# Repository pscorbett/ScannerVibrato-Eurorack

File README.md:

# ScannerVibrato-Eurorack
Scanner vibrato eurorack module that uses digital logic chips (no MCU) to perform the scanning across the LC ladder.

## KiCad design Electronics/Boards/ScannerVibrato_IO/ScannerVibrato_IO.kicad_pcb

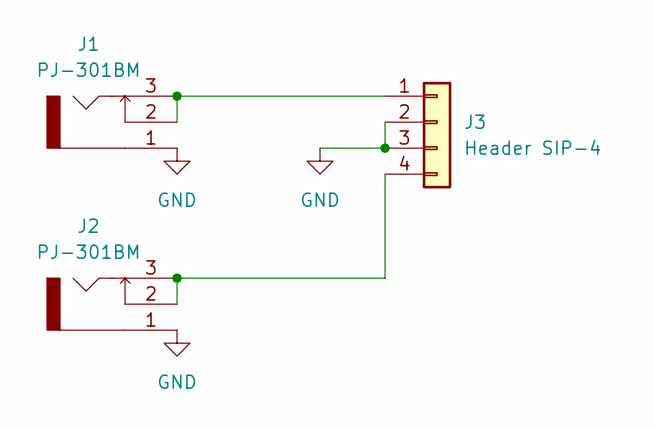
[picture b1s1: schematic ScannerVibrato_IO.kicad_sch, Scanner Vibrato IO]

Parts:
J1, J2: PJ-301BM; Part Number PJ-301BM
J3: Header SIP-4; PinHeader_1x04_P2.54mm_Vertical; Part Number PH1-04-UA

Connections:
GND: J1.1 (S), J2.1 (S), J3.2, J3.3
unnamed: J1.2 (SW), J1.3 (T), J3.1
unnamed: J2.2 (SW), J2.3 (T), J3.4

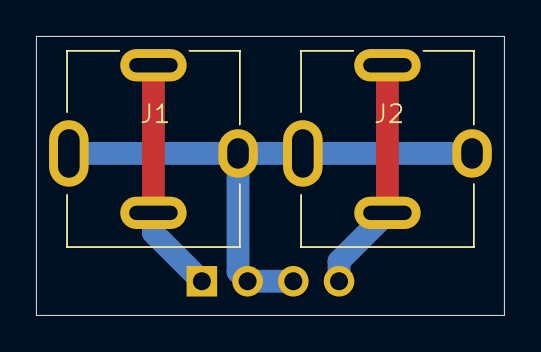
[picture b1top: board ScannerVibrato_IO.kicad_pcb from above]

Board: 2 copper layers, 26.0 x 15.5 mm, 3 parts (1 on the bottom side), 3 nets.

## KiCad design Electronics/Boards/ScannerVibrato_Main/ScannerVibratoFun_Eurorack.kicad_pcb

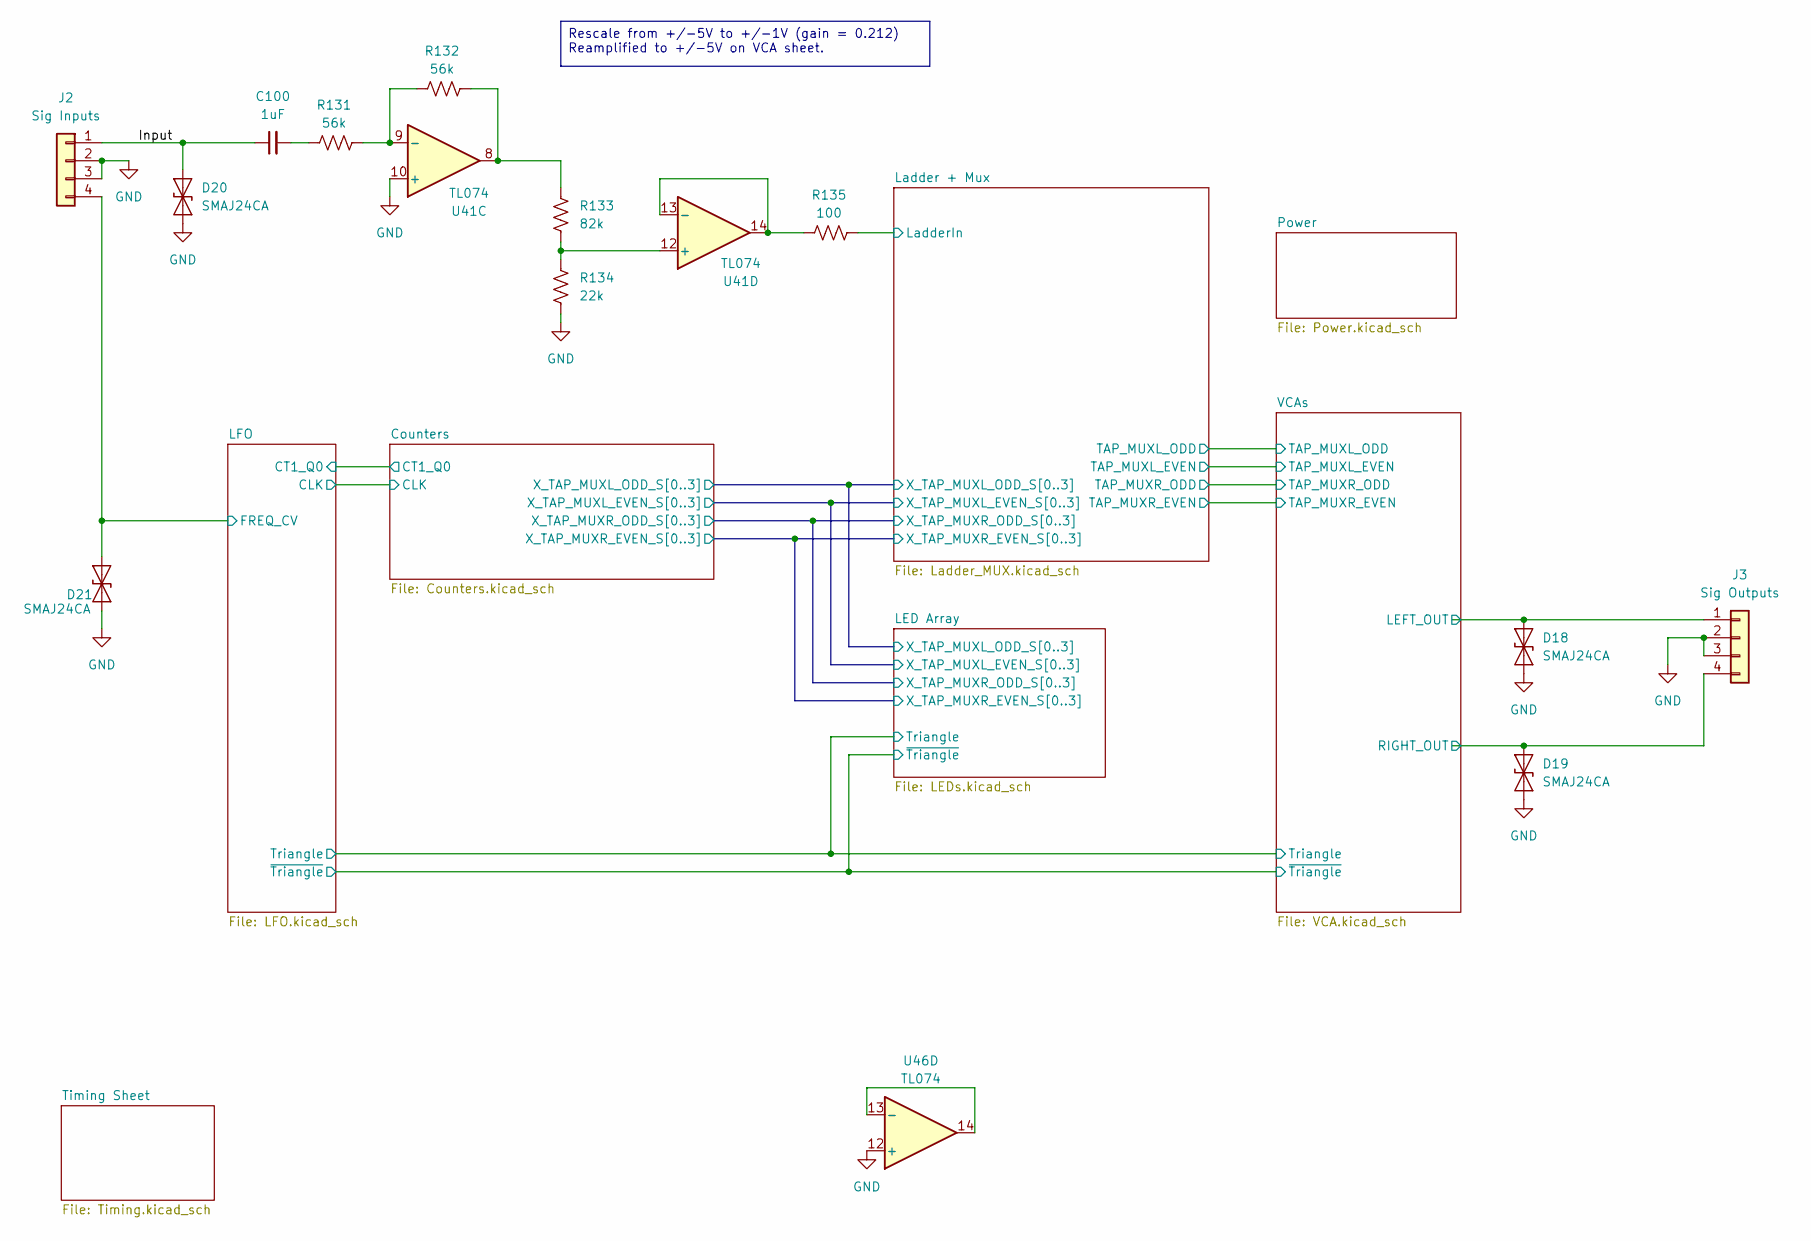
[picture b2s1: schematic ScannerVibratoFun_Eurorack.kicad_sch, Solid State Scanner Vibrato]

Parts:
C100: 1uF; C_0805_2012Metric
D18, D19, D20, D21: SMAJ24CA; D_SMA
J2: Sig Inputs; IO_Jack_Header
J3: Sig Outputs; IO_Jack_Header
R131, R132: 56k; R_0603_1608Metric
R133: 82k; R_0603_1608Metric
R134: 22k; R_0603_1608Metric
R135: 100; R_0603_1608Metric
U41, U46: TL074; TSSOP-14_4.4x5mm_P0.65mm; Part Number TL074HIPWR

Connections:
/Input: C100.1, D20.2 (A2), J2.1
/LFO/FREQ_CV: D21.2 (A2), J2.4; also elsewhere on the board
/Ladder + Mux/LadderIn: R135.2; also elsewhere on the board
/VCAs/LEFT_OUT: D18.2 (A2), J3.1; also elsewhere on the board
/VCAs/RIGHT_OUT: D19.2 (A2), J3.4; also elsewhere on the board
GND: D18.1 (A1), D19.1 (A1), D20.1 (A1), D21.1 (A1), J2.2, J2.3, J3.2, J3.3, R134.1, U41.10 (+), U46.12 (+); also elsewhere on the board
unnamed: C100.2, R131.1
unnamed: R132.2, R133.2, U41.8
unnamed: R131.2, R132.1, U41.9 (-)
unnamed: R133.1, R134.2, U41.12 (+)
unnamed: R135.1, U41.13 (-), U41.14
unnamed: U46.13 (-), U46.14

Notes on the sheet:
Rescale from +/-5V to +/-1V (gain = 0.212) Reamplified to +/-5V on VCA sheet.

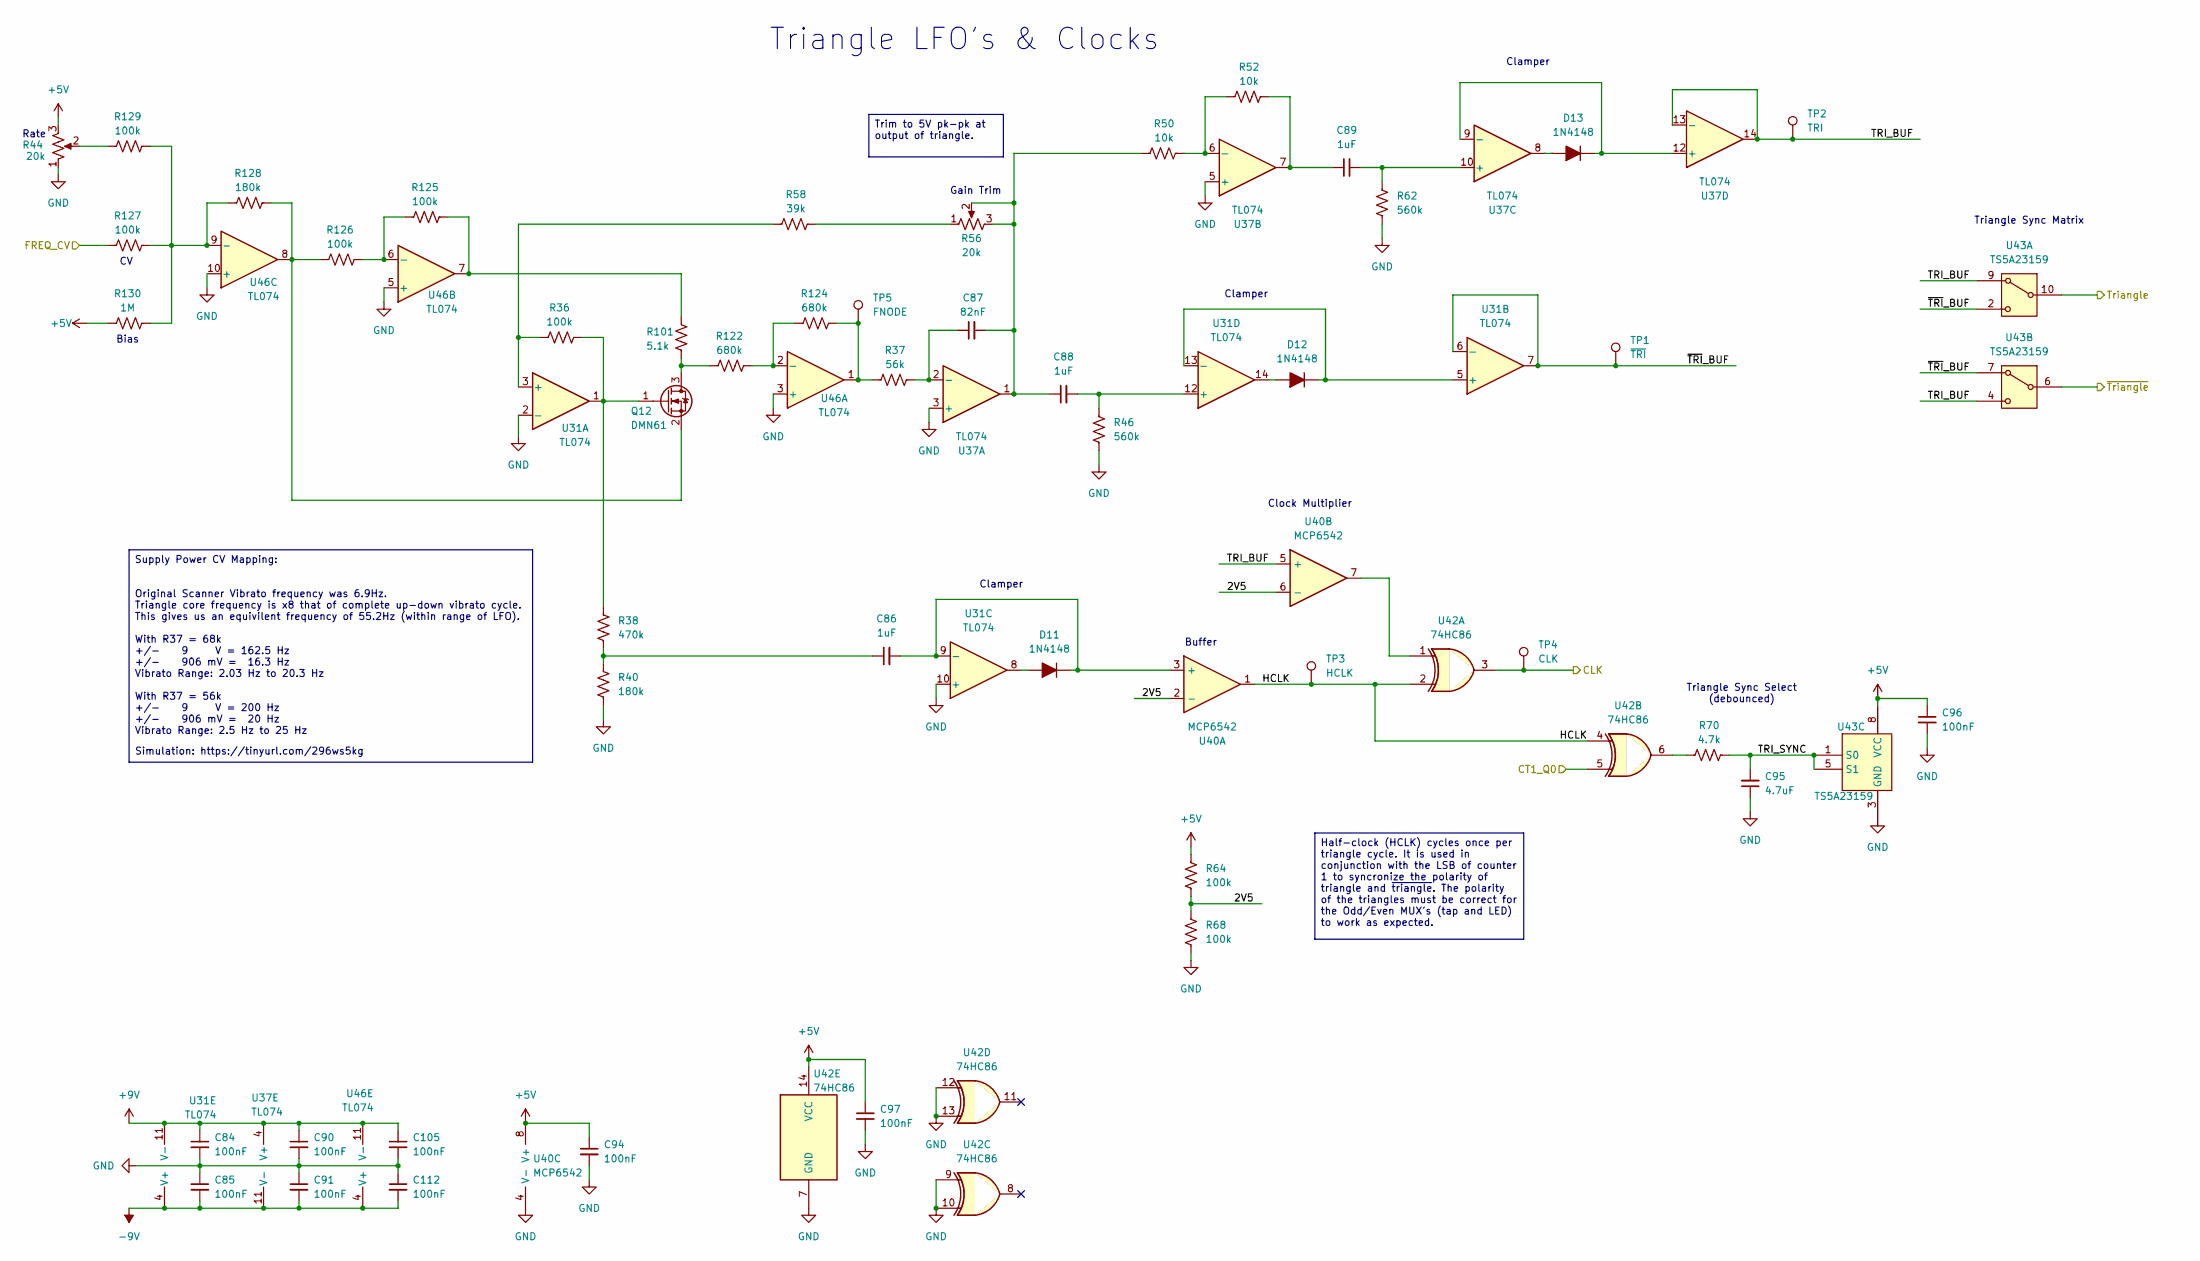
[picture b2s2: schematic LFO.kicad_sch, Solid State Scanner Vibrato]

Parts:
C84, C85, C90, C91, C94, C96, C97, C105, C112: 100nF; C_0603_1608Metric
C86, C88, C89: 1uF; C_0805_2012Metric
C87: 82nF; C_0805_2012Metric
C95: 4.7uF; C_0805_2012Metric
D11, D12, D13: 1N4148; D_SOD-523; Part Number 1N4148WT
Q12: DMN61; SOT-23; Part Number DMN61D9UWQ-13
R36, R64, R68, R125, R126, R127, R129: 100k; R_0603_1608Metric
R37: 56k; R_0603_1608Metric
R38: 470k; R_0603_1608Metric
R40, R128: 180k; R_0603_1608Metric
R44: 20k; 16mm-POT-Right-Angle_LL; Part Number RV16AF-4M-15R1-B20K-EV
R46, R62: 560k; R_0603_1608Metric
R50, R52: 10k; R_0603_1608Metric
R56: 20k; Potentiometer_Bourns_TC33X_Vertical_Fixed3D; Part Number TC33X-2-203E
R58: 39k; R_0603_1608Metric
R70: 4.7k; R_0603_1608Metric
R101: 5.1k; R_0603_1608Metric
R122, R124: 680k; R_0603_1608Metric
R130: 1M; R_0603_1608Metric
TP1: ~{TRI}; 5016; Part Number 5016
TP2: TRI; 5016; Part Number 5016
TP3: HCLK; 5016; Part Number 5016
TP4: CLK; 5016; Part Number 5016
TP5: FNODE; 5016; Part Number 5016
U31, U37, U46: TL074; TSSOP-14_4.4x5mm_P0.65mm; Part Number TL074HIPWR
U40: MCP6542; MSOP-8_3x3mm_P0.65mm; Part Number MCP6542T-I/MS
U42: 74HC86; TSSOP-14_4.4x5mm_P0.65mm; Part Number SN74HC86PWR
U43: TS5A23159; VSSOP-10_3x3mm_P0.5mm; Part Number TS5A23159DGSR

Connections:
+5V: C94.1, C96.1, C97.1, R44.3, R64.2, R130.1, U40.8 (V+), U42.14 (VCC), U43.8 (VCC); also elsewhere on the board
+9V: C84.1, C90.1, C105.1, U31.11 (V-), U37.4 (V+), U46.11 (V-); also elsewhere on the board
-9V: C85.2, C91.2, C112.2, U31.4 (V+), U37.11 (V-), U46.4 (V+); also elsewhere on the board
/Counters/CLK: TP4.1, U42.3; also elsewhere on the board
/Counters/CT1_Q0: U42.5; also elsewhere on the board
/LED Array/Triangle: U43.10 (COM0); also elsewhere on the board
/LED Array/~Triangle: U43.6 (COM1); also elsewhere on the board
/LFO/2V5: R64.1, R68.2, U40.2 (-), U40.6 (-)
/LFO/FREQ_CV: R127.1; also elsewhere on the board
/LFO/HCLK: TP3.1, U40.1, U42.2, U42.4
/LFO/TRI_BUF: TP2.1, U37.13 (-), U37.14, U40.5 (+), U43.4 (NO0), U43.9 (NC0)
/LFO/TRI_SYNC: C95.2, R70.2, U43.1 (S0), U43.5 (S1)
/LFO/~TRI_BUF: TP1.1, U31.6 (-), U31.7, U43.2 (NO0), U43.7 (NC1)
GND: C84.2, C85.1, C90.2, C91.1, C94.2, C95.1, C96.2, C97.2, C105.2, C112.1, R40.1, R44.1, R46.1, R62.1, R68.1, U31.2 (-), U31.10 (+), U37.3 (+), U37.5 (+), U40.4 (V-), U42.7 (GND), U42.9, U42.10, U42.12, U42.13, U43.3 (GND), U46.3 (+), U46.5 (+), U46.10 (+); also elsewhere on the board
unnamed: C86.1, R38.1, R40.2
unnamed: C87.2, C88.1, R50.1, R56.2, R56.3, U37.1
unnamed: C89.1, R52.2, U37.7
unnamed: D11.2 (A), U31.8
unnamed: C86.2, D11.1 (K), U31.9 (-), U40.3 (+)
unnamed: D12.2 (A), U31.14
unnamed: D12.1 (K), U31.5 (+), U31.13 (-)
unnamed: D13.2 (A), U37.8
unnamed: D13.1 (K), U37.9 (-), U37.12 (+)
unnamed: Q12.3 (D), R101.1, R122.1
unnamed: Q12.1 (G), R36.2, R38.2, U31.1
unnamed: Q12.2 (S), R126.1, R128.2, U46.8
unnamed: R56.1, R58.2
unnamed: R70.1, U42.6
unnamed: R101.2, R125.2, U46.7
unnamed: R37.1, R124.2, TP5.1, U46.1
unnamed: R44.2, R129.1
unnamed: R36.1, R58.1, U31.3 (+)
unnamed: C88.2, R46.2, U31.12 (+)
unnamed: C87.1, R37.2, U37.2 (-)
unnamed: R50.2, R52.1, U37.6 (-)
unnamed: C89.2, R62.2, U37.10 (+)
unnamed: U40.7, U42.1
unnamed: R122.2, R124.1, U46.2 (-)
unnamed: R125.1, R126.2, U46.6 (-)
unnamed: R127.2, R128.1, R129.2, R130.2, U46.9 (-)

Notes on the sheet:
Triangle LFO's & Clocks
Clamper
Triangle Sync Select (debounced)
Triangle Sync Matrix
Buffer
Bias
Gain Trim
Clock Multiplier
Simulation: https://tinyurl.com/296ws5kg
Rate
Half-clock (HCLK) cycles once per triangle cycle. It is used in conjunction with the LSB of counter 1 to syncronize the polarity of triangle and ~{triangle}. The polarity of the triangles must be correct for the Odd/Even MUX's (tap and LED) to work as expected.
Trim to 5V pk-pk at output of triangle.
Supply Power CV Mapping: Original Scanner Vibrato frequency was 6.9Hz. Triangle core frequency is x8 that of complete up-down vibrato cycle. This gives us an equivilent frequency of 55.2Hz (within range of LFO). With R37 = 68k +/- 9 V = 162.5 Hz +/- 906 mV = 16.3 Hz Vibrato Range: 2.03 Hz to 20.3 H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

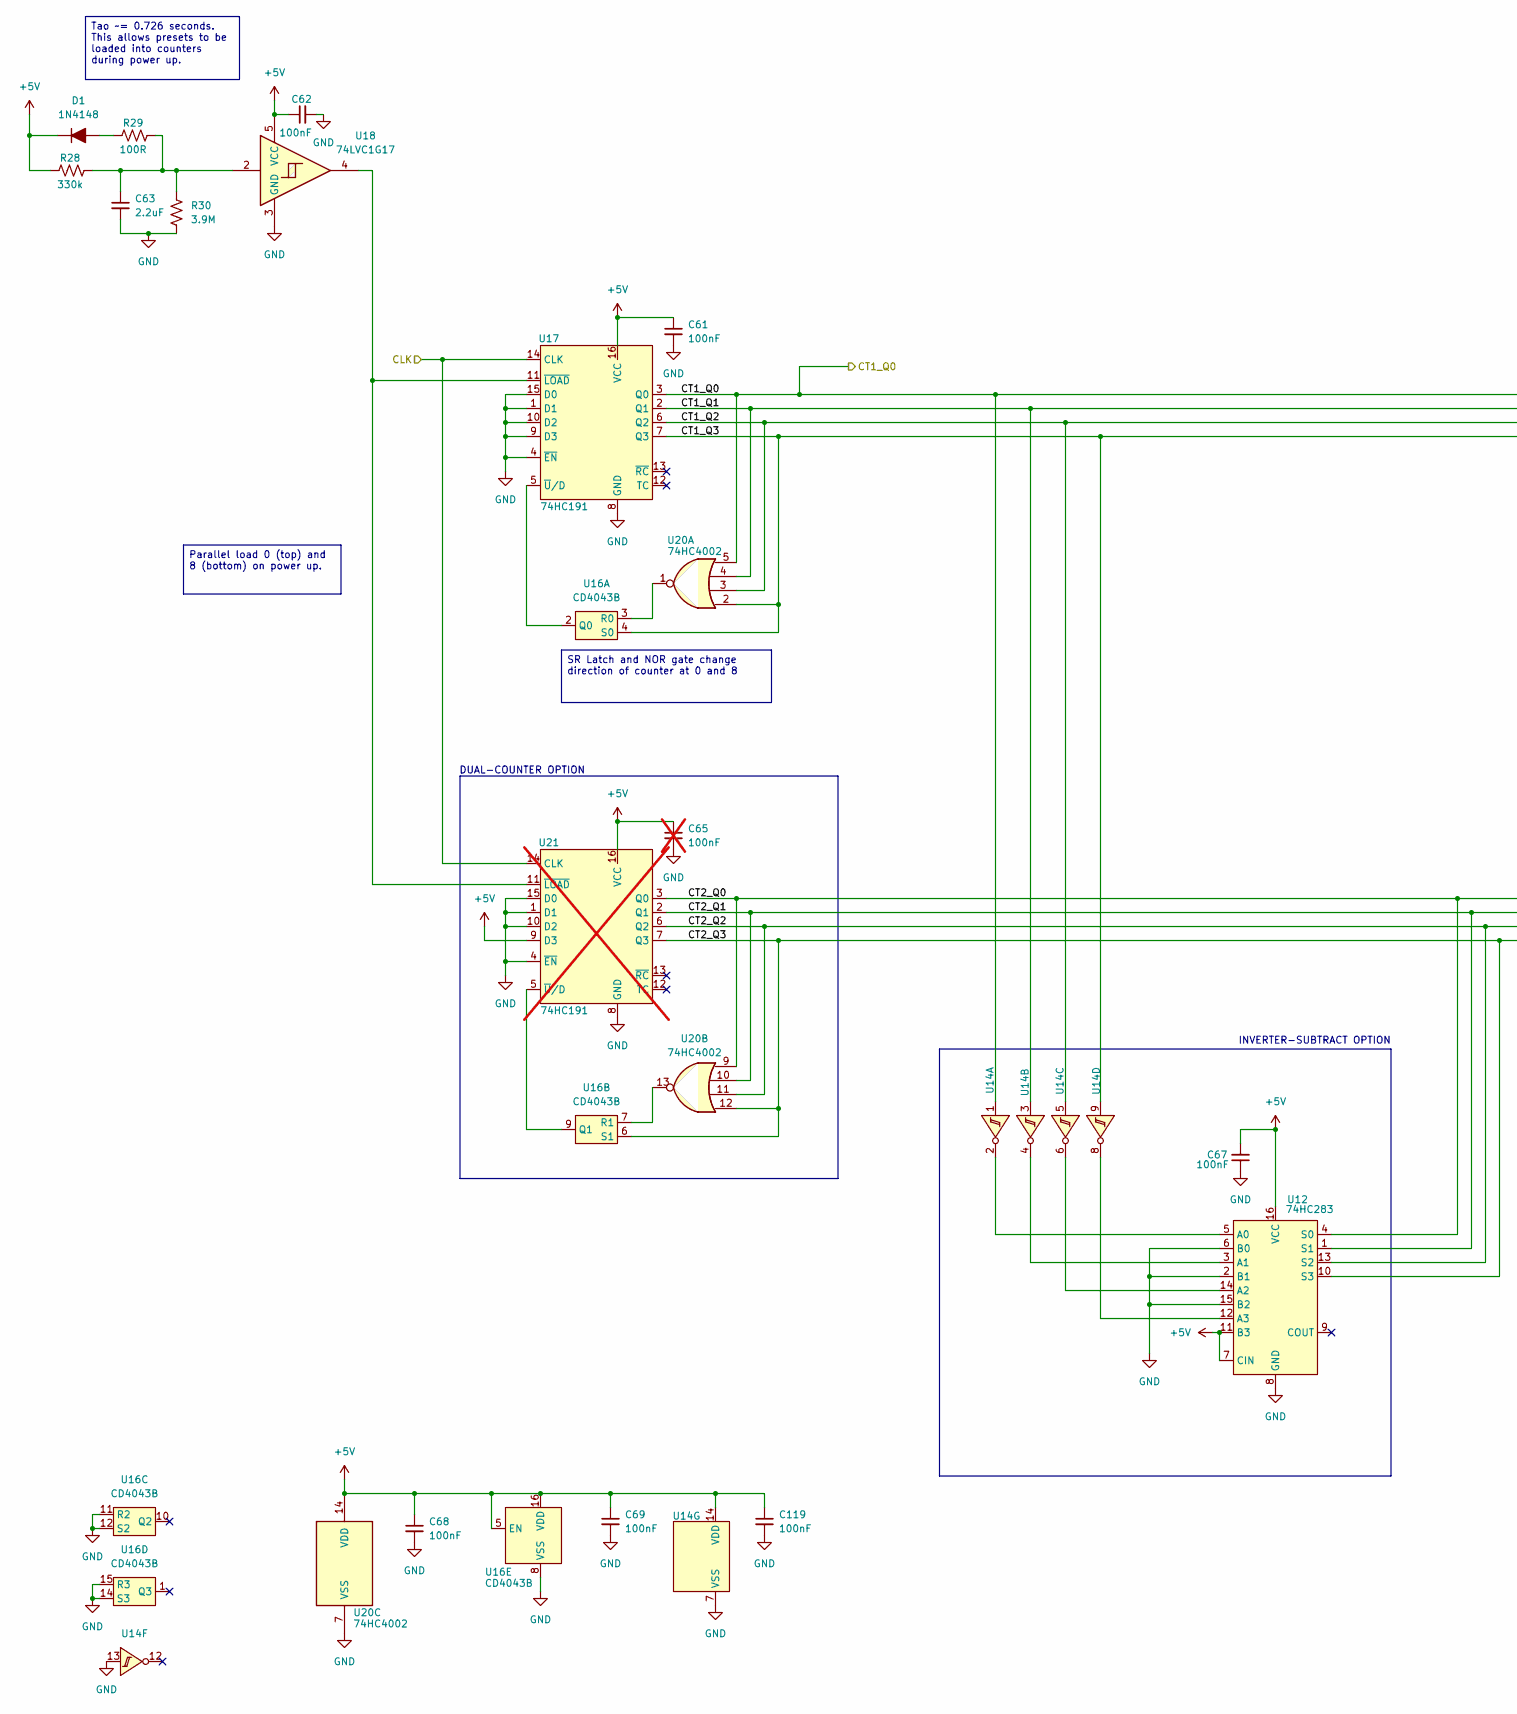
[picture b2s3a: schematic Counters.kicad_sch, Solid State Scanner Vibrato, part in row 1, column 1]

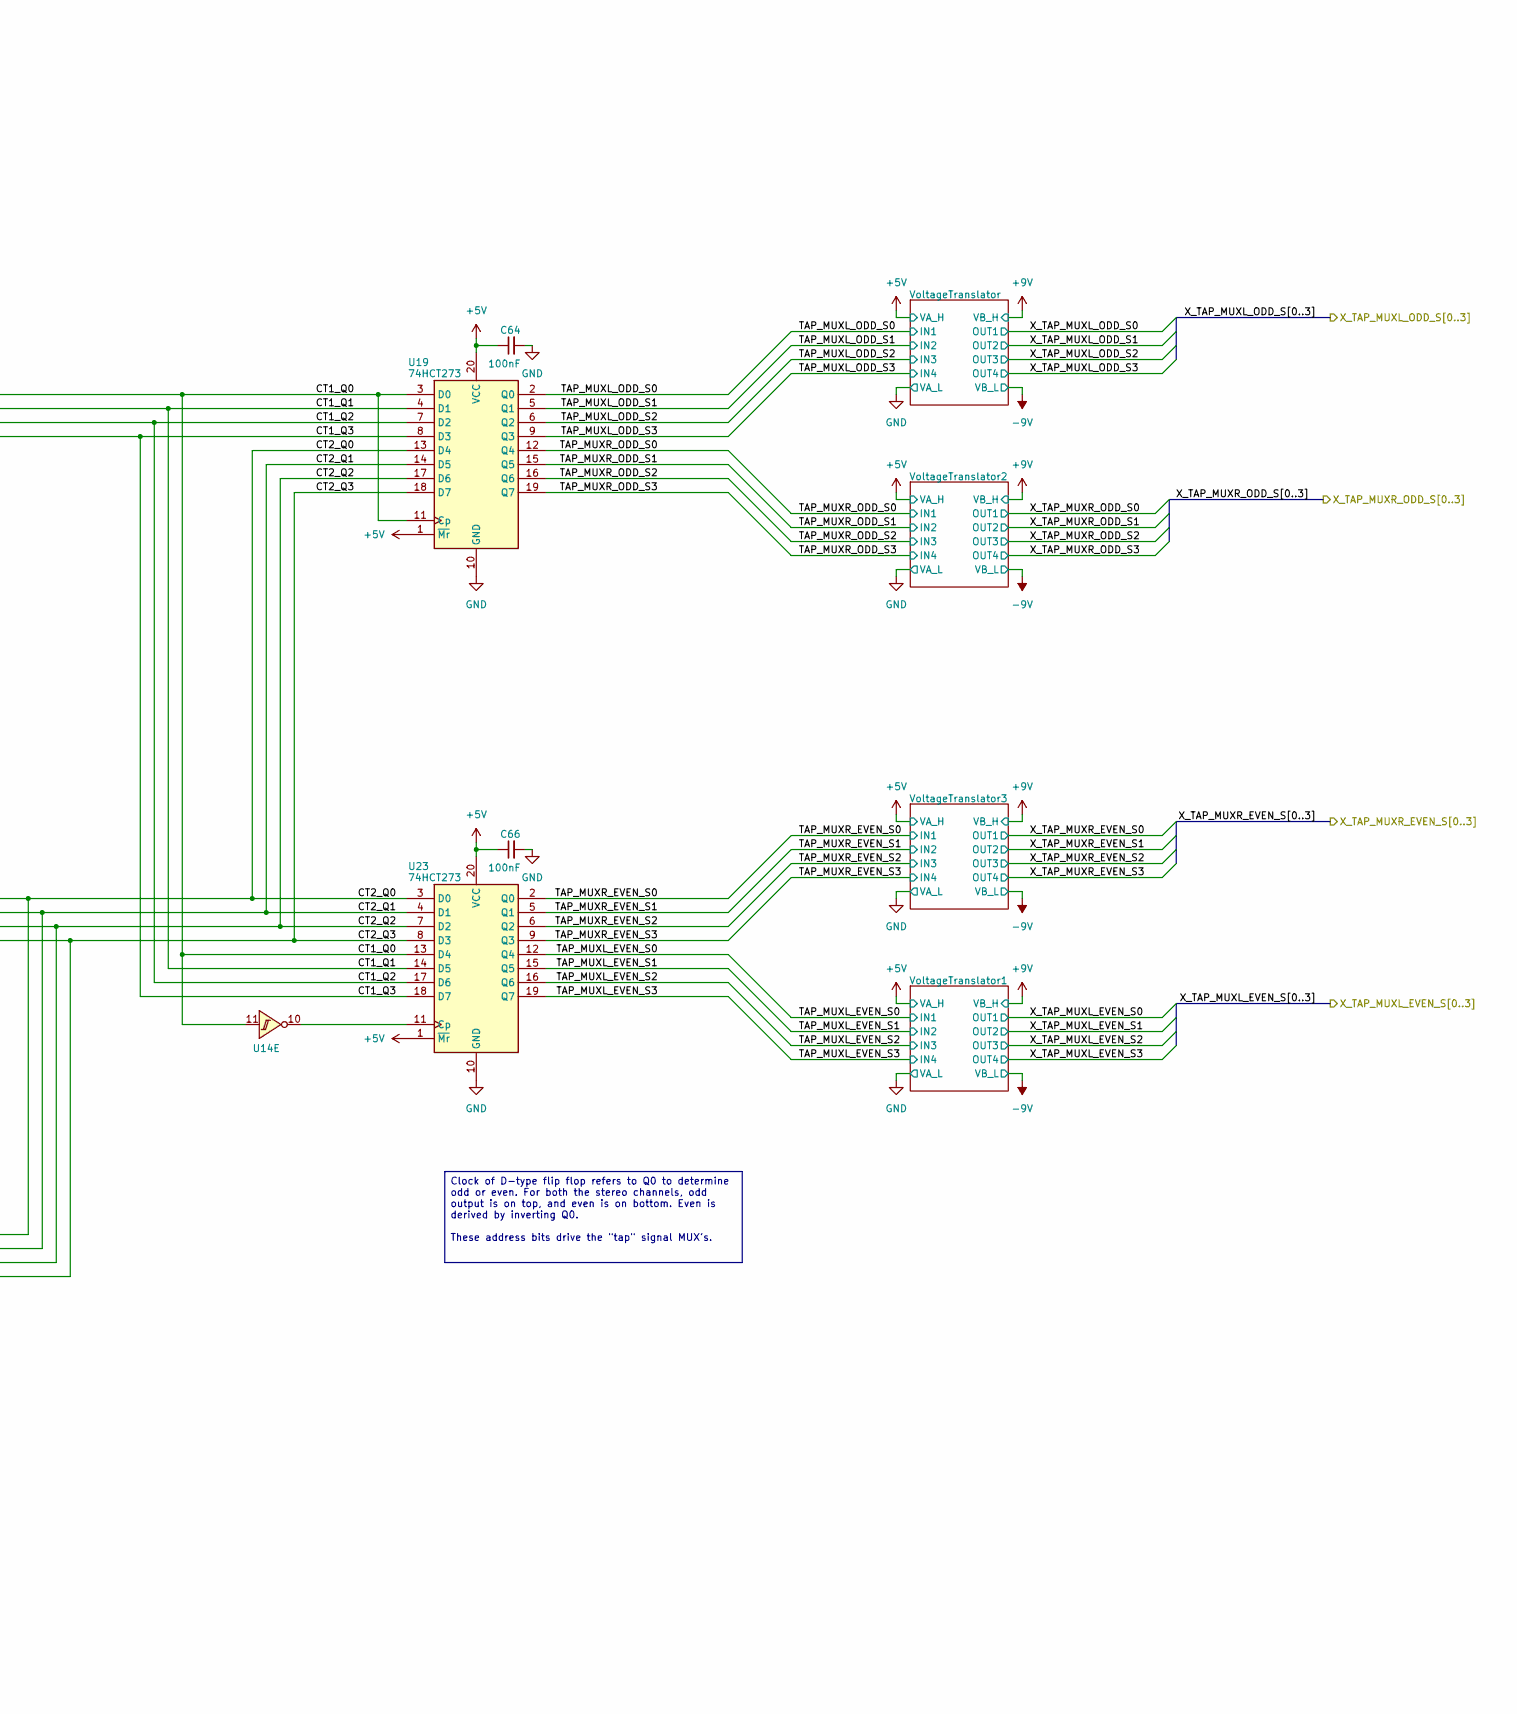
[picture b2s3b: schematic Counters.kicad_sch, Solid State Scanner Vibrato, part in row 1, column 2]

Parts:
C61, C62, C64, C66, C67, C68, C69, C119: 100nF; C_0603_1608Metric
C63: 2.2uF; C_0805_2012Metric
C65: 100nF; C_0603_1608Metric; not fitted
D1: 1N4148; D_SOD-523; Part Number 1N4148WT
R28: 330k; R_0603_1608Metric
R29: 100R; R_0603_1608Metric
R30: 3.9M; R_0603_1608Metric
U12: 74HC283; SOIC-16_3.9x9.9mm_P1.27mm; Part Number CD74HC283M96
U14: CD40106; TSSOP-14_4.4x5mm_P0.65mm; Part Number CD40106BPWR
U16: CD4043B; TSSOP-16_4.4x5mm_P0.65mm; Part Number CD4043BPWR
U17: 74HC191; TSSOP-16_4.4x5mm_P0.65mm; Part Number 74HC191PW,118
U18: 74LVC1G17; SOT-353_SC-70-5; Part Number SN74LVC1G17DCKR
U19, U23: 74HCT273; TSSOP-20_4.4x6.5mm_P0.65mm; Part Number SN74HCT273PWR
U20: 74HC4002; TSSOP-14_4.4x5mm_P0.65mm; Part Number CD74HC4002PWR
U21: 74HC191; TSSOP-16_4.4x5mm_P0.65mm; Part Number 74HC191PW,118; not fitted

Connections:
+5V: C61.1, C62.1, C64.1, C65.1, C66.1, C67.2, C68.1, C69.1, C119.1, D1.1 (K), R28.1, U12.7 (CIN), U12.11 (B3), U12.16 (VCC), U14.14 (VDD), U16.5 (EN), U16.16 (VDD), U17.16 (VCC), U18.5 (VCC), U19.1 (~Mr), U19.20 (VCC), U20.14 (VDD), U21.9 (D3), U21.16 (VCC), U23.1 (~Mr), U23.20 (VCC); also elsewhere on the board
/Counters/CLK: U17.14 (CLK), U21.14 (CLK); also elsewhere on the board
/Counters/CT1_Q0: U14.1 (A), U14.11 (E), U17.3 (Q0), U19.3 (D0), U19.11 (Cp), U20.5, U23.13 (D4); also elsewhere on the board
/Counters/CT1_Q1: U14.3 (B), U17.2 (Q1), U19.4 (D1), U20.4, U23.14 (D5)
/Counters/CT1_Q2: U14.5 (C), U17.6 (Q2), U19.7 (D2), U20.3, U23.17 (D6)
/Counters/CT1_Q3: U14.9 (D), U16.4 (S0), U17.7 (Q3), U19.8 (D3), U20.2, U23.18 (D7)
/Counters/CT2_Q0: U12.4 (S0), U19.13 (D4), U20.9, U21.3 (Q0), U23.3 (D0)
/Counters/CT2_Q1: U12.1 (S1), U19.14 (D5), U20.10, U21.2 (Q1), U23.4 (D1)
/Counters/CT2_Q2: U12.13 (S2), U19.17 (D6), U20.11, U21.6 (Q2), U23.7 (D2)
/Counters/CT2_Q3: U12.10 (S3), U16.6 (S1), U19.18 (D7), U20.12, U21.7 (Q3), U23.8 (D3)
/Counters/TAP_MUXL_EVEN_S0: U23.12 (Q4); also elsewhere on the board
/Counters/TAP_MUXL_EVEN_S1: U23.15 (Q5); also elsewhere on the board
/Counters/TAP_MUXL_EVEN_S2: U23.16 (Q6); also elsewhere on the board
/Counters/TAP_MUXL_EVEN_S3: U23.19 (Q7); also elsewhere on the board
/Counters/TAP_MUXL_ODD_S0: U19.2 (Q0); also elsewhere on the board
/Counters/TAP_MUXL_ODD_S1: U19.5 (Q1); also elsewhere on the board
/Counters/TAP_MUXL_ODD_S2: U19.6 (Q2); also elsewhere on the board
/Counters/TAP_MUXL_ODD_S3: U19.9 (Q3); also elsewhere on the board
/Counters/TAP_MUXR_EVEN_S0: U23.2 (Q0); also elsewhere on the board
/Counters/TAP_MUXR_EVEN_S1: U23.5 (Q1); also elsewhere on the board
/Counters/TAP_MUXR_EVEN_S2: U23.6 (Q2); also elsewhere on the board
/Counters/TAP_MUXR_EVEN_S3: U23.9 (Q3); also elsewhere on the board
/Counters/TAP_MUXR_ODD_S0: U19.12 (Q4); also elsewhere on the board
/Counters/TAP_MUXR_ODD_S1: U19.15 (Q5); also elsewhere on the board
/Counters/TAP_MUXR_ODD_S2: U19.16 (Q6); also elsewhere on the board
/Counters/TAP_MUXR_ODD_S3: U19.19 (Q7); also elsewhere on the board
GND: C61.2, C62.2, C63.2, C64.2, C65.2, C66.2, C67.1, C68.2, C69.2, C119.2, R30.2, U12.2 (B1), U12.6 (B0), U12.8 (GND), U12.15 (B2), U14.7 (VSS), U14.13 (F), U16.8 (VSS), U16.11 (R2), U16.12 (S2), U16.14 (S3), U16.15 (R3), U17.1 (D1), U17.4 (~EN), U17.8 (GND), U17.9 (D3), U17.10 (D2), U17.15 (D0), U18.3 (GND), U19.10 (GND), U20.7 (VSS), U21.1 (D1), U21.4 (~EN), U21.8 (GND), U21.10 (D2), U21.15 (D0), U23.10 (GND); also elsewhere on the board
unnamed: C63.1, R28.2, R29.2, R30.1, U18.2
unnamed: D1.2 (A), R29.1
unnamed: U12.5 (A0), U14.2 (~A)
unnamed: U12.3 (A1), U14.4 (~B)
unnamed: U12.14 (A2), U14.6 (~C)
unnamed: U12.12 (A3), U14.8 (~D)
unnamed: U14.10 (~E), U23.11 (Cp)
unnamed: U16.2 (Q0), U17.5 (~U/D)
unnamed: U16.3 (R0), U20.1
unnamed: U16.9 (Q1), U21.5 (~U/D)
unnamed: U16.7 (R1), U20.13
unnamed: U17.11 (~LOAD), U18.4, U21.11 (~LOAD)

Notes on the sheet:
DUAL-COUNTER OPTION
INVERTER-SUBTRACT OPTION
Tao ~= 0.726 seconds. This allows presets to be loaded into counters during power up.
SR Latch and NOR gate change direction of counter at 0 and 8
Clock of D-type flip flop refers to Q0 to determine odd or even. For both the stereo channels, odd output is on top, and even is on bottom. Even is derived by inverting Q0. These address bits drive the "tap" signal MUX's.
Parallel load 0 (top) and 8 (bottom) on power up.

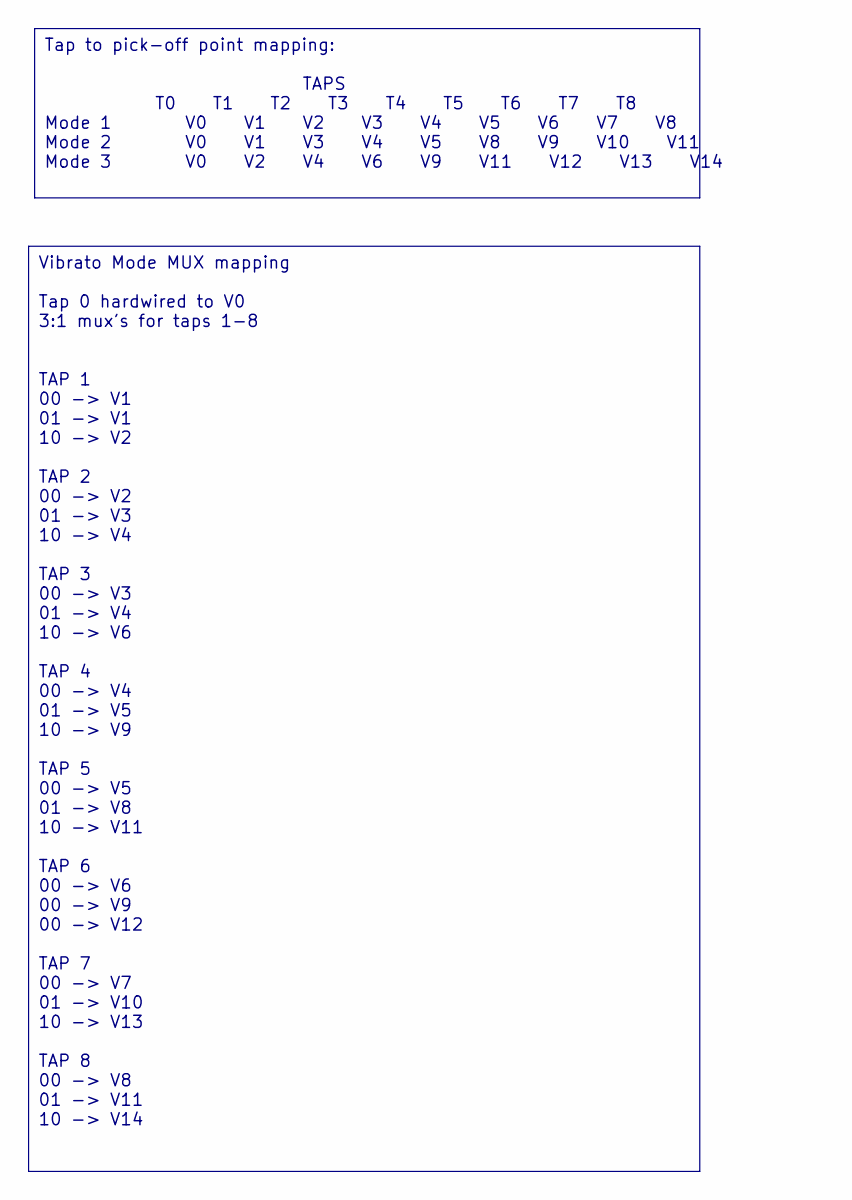
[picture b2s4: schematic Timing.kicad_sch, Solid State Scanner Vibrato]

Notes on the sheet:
Tap to pick-off point mapping: TAPS T0 T1 T2 T3 T4 T5 T6 T7 T8 Mode 1 V0 V1 V2 V3 V4 V5 V6 V7 V8 Mode 2 V0 V1 V3 V4 V5 V8 V9 V10 V11 Mode 3 V0 V2 V4 V6 V9 V11 V12 V13 V14
Vibrato Mode MUX mapping Tap 0 hardwired to V0 3:1 mux's for taps 1-8 TAP 1 00 -> V1 01 -> V1 10 -> V2 TAP 2 00 -> V2 01 -> V3 10 -> V4 TAP 3 00 -> V3 01 -> V4 10 -> V6 TAP 4 00 -> V4 01 -> V5 10 -> V9 TAP 5 00 -> V5 01 -> V8 10 -> V11 TAP 6 00 -> V6 00 -> V9 00 -> V12 TAP 7 00 -> V7 01 -> V10 10 -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

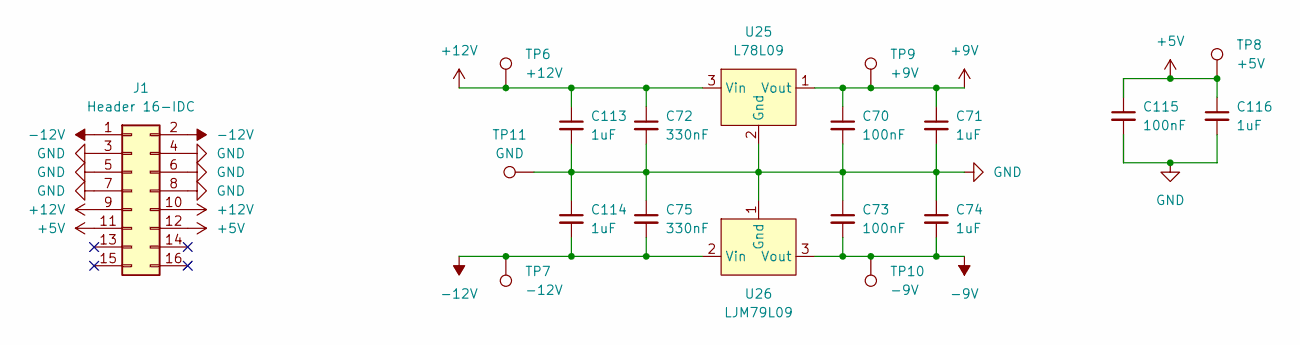
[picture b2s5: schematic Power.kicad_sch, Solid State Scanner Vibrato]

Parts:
C70, C73, C115: 100nF; C_0603_1608Metric
C71, C74, C113, C114, C116: 1uF; C_0805_2012Metric
C72, C75: 330nF; C_0805_2012Metric
J1: Header 16-IDC; IDC-Header_2x08_P2.54mm_Vertical_SMD; Part Number 3020-16-0300-00
TP6: +12V; 5016; Part Number 5016
TP7: -12V; 5016; Part Number 5016
TP8: +5V; 5016; Part Number 5016
TP9: +9V; 5016; Part Number 5016
TP10: -9V; 5016; Part Number 5016
TP11: GND; 5016; Part Number 5016
U25: L78L09; SOT-89-3; Part Number L78L09ACUTR
U26: LJM79L09; SOT-89-3; Part Number NJM79L09SU3-TE1

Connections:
+5V: C115.1, C116.1, J1.11, J1.12, TP8.1; also elsewhere on the board
+9V: C70.1, C71.1, TP9.1, U25.1 (Vout); also elsewhere on the board
+12V: C72.1, C113.1, J1.9, J1.10, TP6.1, U25.3 (Vin)
-9V: C73.2, C74.2, TP10.1, U26.3 (Vout); also elsewhere on the board
-12V: C75.2, C114.2, J1.1, J1.2, TP7.1, U26.2 (Vin)
GND: C70.2, C71.2, C72.2, C73.1, C74.1, C75.1, C113.2, C114.1, C115.2, C116.2, J1.3, J1.4, J1.5, J1.6, J1.7, J1.8, TP11.1, U25.2 (Gnd), U26.1 (Gnd); also elsewhere on the board
